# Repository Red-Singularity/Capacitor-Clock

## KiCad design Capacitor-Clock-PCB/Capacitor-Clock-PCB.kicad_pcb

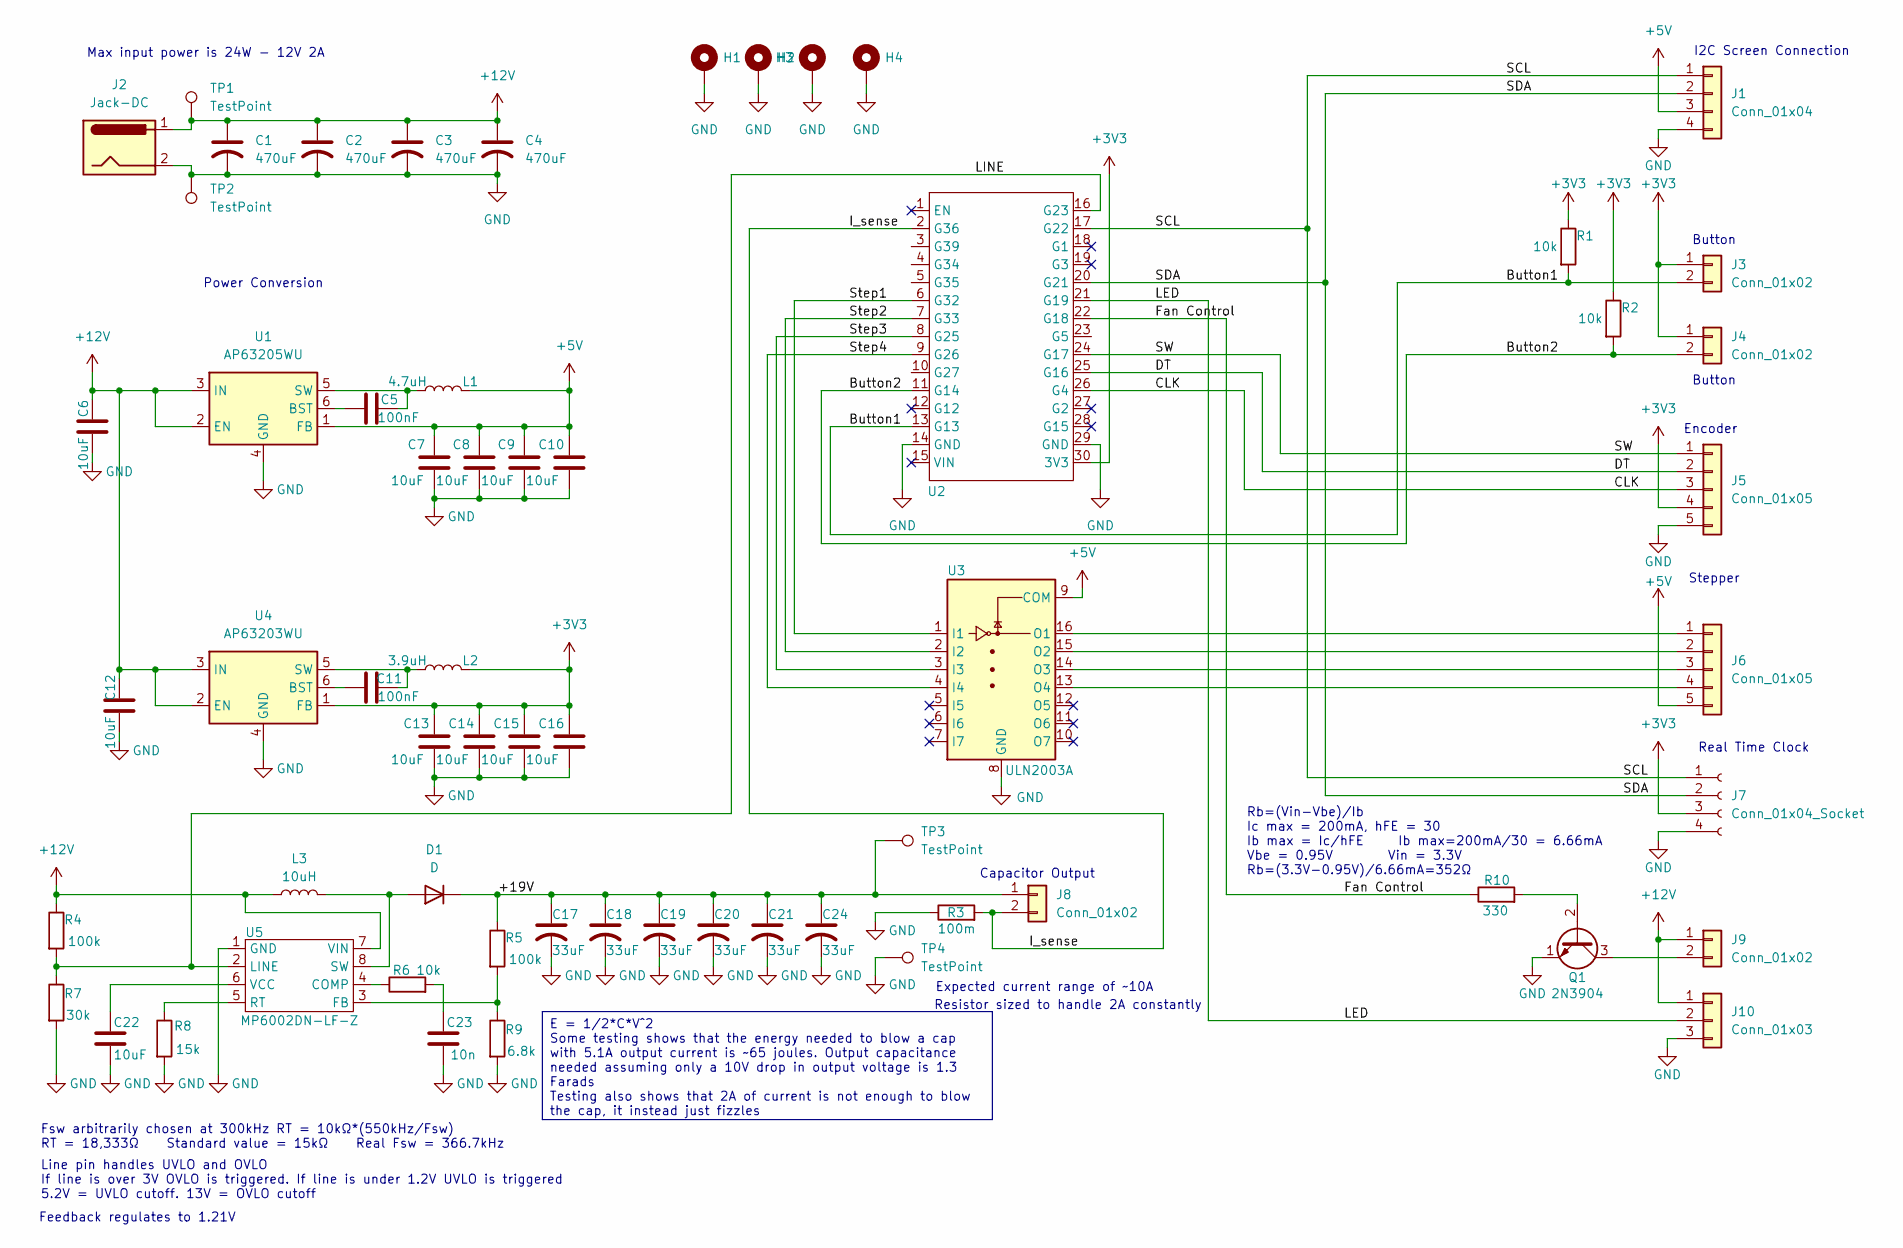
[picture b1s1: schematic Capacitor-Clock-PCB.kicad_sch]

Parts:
C1, C2, C3, C4: 470uF; CP_Radial_Tantal_D8.0mm_P2.50mm
C5, C11: 100nF; C_Disc_D5.1mm_W3.2mm_P5.00mm
C6, C7, C8, C9, C10, C12, C13, C14, C15, C16, C22: 10uF; C_Disc_D5.1mm_W3.2mm_P5.00mm
C17, C18, C19, C20, C21, C24: 33uF; CP_Radial_Tantal_D5.0mm_P2.50mm
C23: 10n; C_Disc_D5.1mm_W3.2mm_P5.00mm
D1: D; D_A-405_P7.62mm_Horizontal
H1, H2, H3, H4: MountingHole_Pad; MountingHole_3.2mm_M3_DIN965_Pad
J1: Conn_01x04; JST_XH_B4B-XH-A_1x04_P2.50mm_Vertical
J2: Jack-DC; BarrelJack_CUI_PJ-063AH_Horizontal
J3, J4, J9: Conn_01x02; JST_XH_B2B-XH-A_1x02_P2.50mm_Vertical
J5, J6: Conn_01x05; JST_XH_B5B-XH-A_1x05_P2.50mm_Vertical
J7: Conn_01x04_Socket; PinSocket_1x04_P2.54mm_Vertical
J8: Conn_01x02; PinSocket_1x02_P2.54mm_Vertical
J10: Conn_01x03; JST_XH_B3B-XH-A_1x03_P2.50mm_Vertical
L1: 4.7uH; IND_SRR4818A-3R3Y
L2: 3.9uH; IND_SRR4818A-3R3Y
L3: 10uH; L_Radial_D8.7mm_P5.00mm_Fastron_07HCP
Q1: 2N3904; TO-92_Inline
R1, R2, R6: 10k; R_Axial_DIN0207_L6.3mm_D2.5mm_P7.62mm_Horizontal
R3: 100m; R_2512_6332Metric
R4, R5: 100k; R_Axial_DIN0207_L6.3mm_D2.5mm_P7.62mm_Horizontal
R7: 30k; R_Axial_DIN0207_L6.3mm_D2.5mm_P7.62mm_Horizontal
R8: 15k; R_Axial_DIN0207_L6.3mm_D2.5mm_P7.62mm_Horizontal
R9: 6.8k; R_Axial_DIN0207_L6.3mm_D2.5mm_P7.62mm_Horizontal
R10: 330; R_Axial_DIN0207_L6.3mm_D2.5mm_P7.62mm_Horizontal
TP1, TP2, TP3, TP4: TestPoint
U1: AP63205WU; TSOT-23-6
U2: MODULE_ESP32_DEVKIT_V1
U3: ULN2003A; DIP-16_W7.62mm
U4: AP63203WU; TSOT-23-6
U5: MP6002DN-LF-Z; SOIC-8-1EP_3.9x4.9mm_P1.27mm_EP2.41x3.3mm

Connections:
+3V3: C13.2, C14.2, C15.2, C16.2, J3.1, J4.1, J5.4, J7.3, L2.2, R1.1, R2.1, U2.30 (3V3), U4.1 (FB)
+5V: C7.2, C8.2, C9.2, C10.2, J1.3, J6.5, L1.2, U1.1 (FB), U3.9 (COM)
+12V: C1.1, C2.1, C3.1, C4.1, C6.2, C12.2, J2.1, J9.1, J10.1, L3.1, R4.1, TP1.1, U1.2 (EN), U1.3 (IN), U4.2 (EN), U4.3 (IN), U5.7 (VIN)
/+19V: C17.1, C18.1, C19.1, C20.1, C21.1, C24.1, D1.1 (K), J8.1, R5.1, TP3.1
/Button1: J3.2, R1.2, U2.13 (G13)
/Button2: J4.2, R2.2, U2.11 (G14)
/CLK: J5.3, U2.26 (G4)
/DT: J5.2, U2.25 (G16)
/Fan Control: R10.1, U2.22 (G18)
/I_sense: J8.2, R3.2, U2.2 (G36)
/LED: J10.2, U2.21 (G19)
/LINE: R4.2, R7.1, U2.16 (G23), U5.2 (LINE)
/SCL: J1.1, J7.1, U2.17 (G22)
/SDA: J1.2, J7.2, U2.20 (G21)
/SW: J5.1, U2.24 (G17)
/Step1: U2.6 (G32), U3.1 (I1)
/Step2: U2.7 (G33), U3.2 (I2)
/Step3: U2.8 (G25), U3.3 (I3)
/Step4: U2.9 (G26), U3.4 (I4)
GND: C1.2, C2.2, C3.2, C4.2, C6.1, C7.1, C8.1, C9.1, C10.1, C12.1, C13.1, C14.1, C15.1, C16.1, C17.2, C18.2, C19.2, C20.2, C21.2, C22.1, C23.1, C24.2, H1.1, H2.1, H3.1, H4.1, J1.4, J2.2, J5.5, J7.4, J10.3, Q1.1 (E), R3.1, R7.2, R8.2, R9.2, TP2.1, TP4.1, U1.4 (GND), U2.14 (GND), U2.29 (GND), U3.8 (GND), U4.4 (GND), U5.1 (GND)
unnamed: C23.2, R6.2
unnamed: D1.2 (A), L3.2, U5.8 (SW)
unnamed: J6.1, U3.16 (O1)
unnamed: J6.2, U3.15 (O2)
unnamed: J6.3, U3.14 (O3)
unnamed: J6.4, U3.13 (O4)
unnamed: J9.2, Q1.3 (C)
unnamed: Q1.2 (B), R10.2
unnamed: C5.1, U1.6 (BST)
unnamed: C5.2, L1.1, U1.5 (SW)
unnamed: C11.1, U4.6 (BST)
unnamed: C11.2, L2.1, U4.5 (SW)
unnamed: R6.1, U5.4 (COMP)
unnamed: R5.2, R9.1, U5.3 (FB)
unnamed: R8.1, U5.5 (RT)
unnamed: C22.2, U5.6 (VCC)

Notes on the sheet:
Button
Expected current range of ~10A
Fsw arbitrarily chosen at 300kHz RT = 10kΩ*(550kHz/Fsw) RT = 18,333Ω Standard value = 15kΩ Real Fsw = 366.7kHz
I2C Screen Connection
Capacitor Output
Max input power is 24W - 12V 2A
Resistor sized to handle 2A constantly
Feedback regulates to 1.21V
Rb=(Vin-Vbe)/Ib Ic max = 200mA, hFE = 30 Ib max = Ic/hFE Ib max=200mA/30 = 6.66mA Vbe = 0.95V Vin = 3.3V Rb=(3.3V-0.95V)/6.66mA=352Ω
Encoder
Real Time Clock
Stepper
Line pin handles UVLO and OVLO If line is over 3V OVLO is triggered. If line is under 1.2V UVLO is triggered 5.2V = UVLO cutoff. 13V = OVLO cutoff
Power Conversion
E = 1/2*C*V^2 Some testing shows that the energy needed to blow a cap with 5.1A output current is ~65 joules. Output capacitance needed assuming only a 10V drop in output voltage is 1.3 Farads Testing also shows that 2A of current is not enough to blow the cap, it instead just fizzles

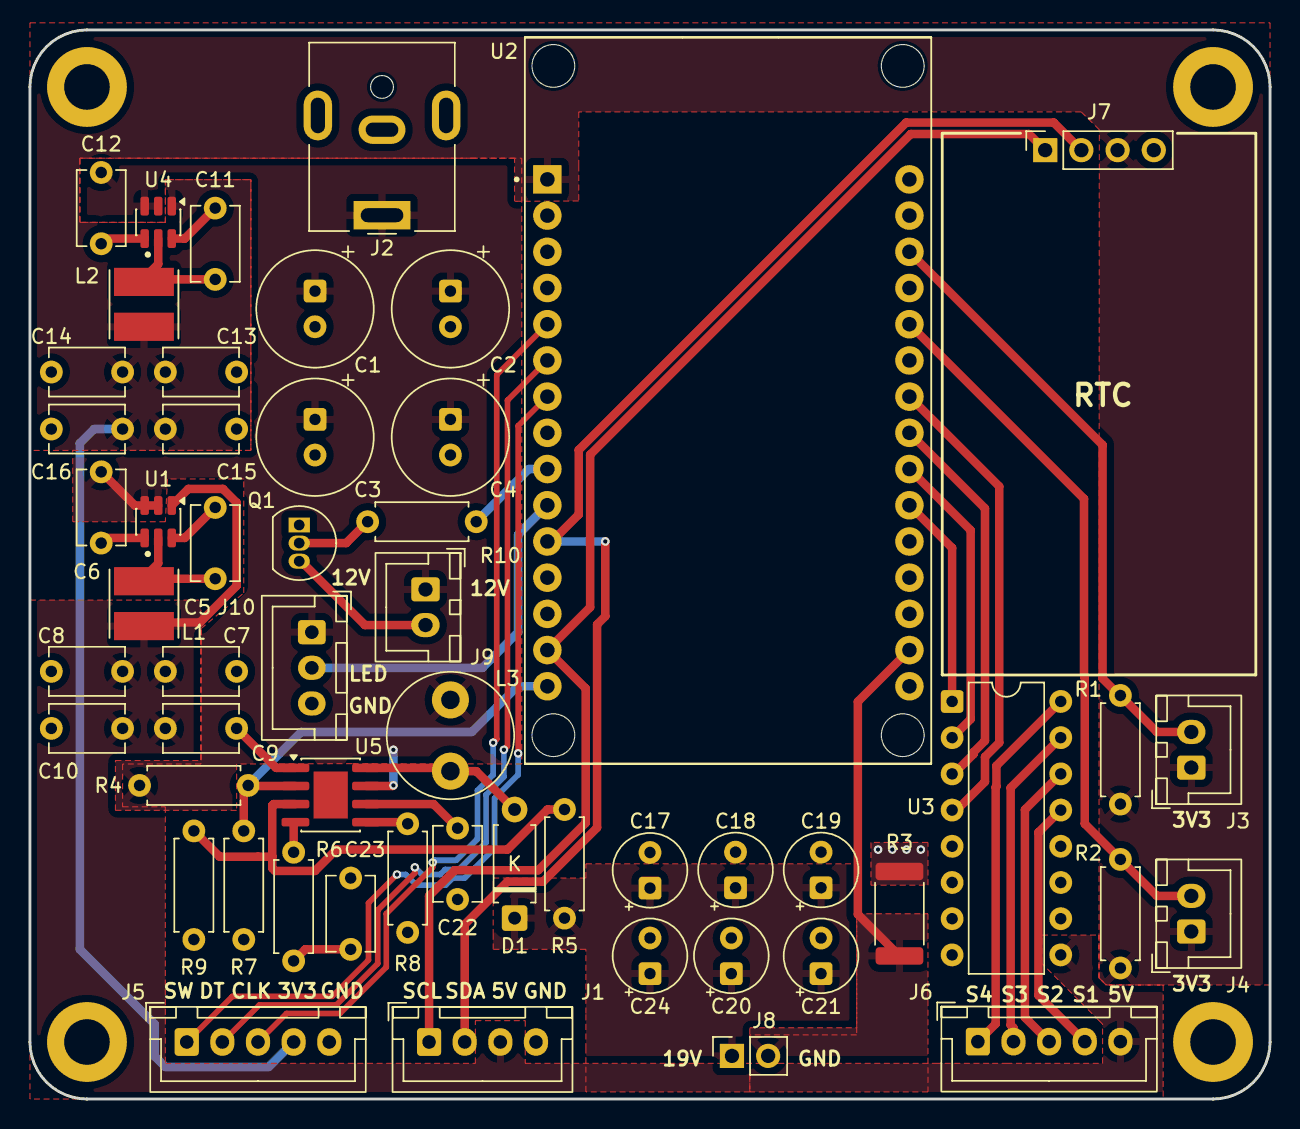
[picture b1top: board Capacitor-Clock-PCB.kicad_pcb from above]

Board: 2 copper layers, 87.0 x 75.0 mm, 58 parts (0 on the bottom side), 36 nets.

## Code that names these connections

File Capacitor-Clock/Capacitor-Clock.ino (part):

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#include <RotaryEncoder.h> // include library for rotary encoder

#define MotorInterfaceType 4 // defines stepper as a 4 wire
#define I_sense 36 // current sense pin
#define Step1 32 // stepper output 1
#define Step2 33 // stepper output 2
#define Step3 25 // stepper output 3
#define Step4 26 // stepper output 4
#define Button_1 13 // generic button input 1
#define Button_2 14 // generic button input 2
#define LED 19 // logic pin for LED output
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  Wire.begin(); // start I2C interface

  //pinmode setup
  pinMode(Step1, OUTPUT);
  pinMode(Step2, OUTPUT);
  pinMode(Step3, OUTPUT);
  pinMode(Step4, OUTPUT);
  pinMode(Button_1, INPUT);
  pinMode(Button_2, INPUT);
  pinMode(LED, OUTPUT);
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
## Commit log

2026-02-25 adjusted code to display to lcd
    began filling out code and was able to make code that displayed to a 2x16 display that can display the general GUI
2026-02-28 quick up date
2026-02-28 new display setup
    setup display using the 20x4 lcd instead 16x2
2026-02-28 continued adjustment to display
    added set and get function to display and set default time
2026-03-09 Preliminary Schematic Finished
    Finished the schematic for the clock and is ready for review. going to continue to pcb layout in meantime
2026-03-09 picked induictor and diode
2026-03-09 board component placement
    finished preliminary component placement. ready for routing
2026-03-09 finished preliminary routing
    finished routing ready for review
2026-03-09 export of step
2026-03-11 Update post design review
    updated schematic and pcb with notes from review. added switchable fan header, ability to control output prongs, and RGB header
2026-03-11 PCB ordered
    Ordered PCB
2026-03-19 sync
2026-03-20 encoder and cursor
2026-03-21 working time adjust
    got time adjustment with encoder to work
2026-03-22 fully working clock with no alarm
    got all clock adjustment and UI functions working. half way through alarm setting
2026-03-23 post 6am sprint
    got all clock functions and UI elements working. made basic stepper control as a result
